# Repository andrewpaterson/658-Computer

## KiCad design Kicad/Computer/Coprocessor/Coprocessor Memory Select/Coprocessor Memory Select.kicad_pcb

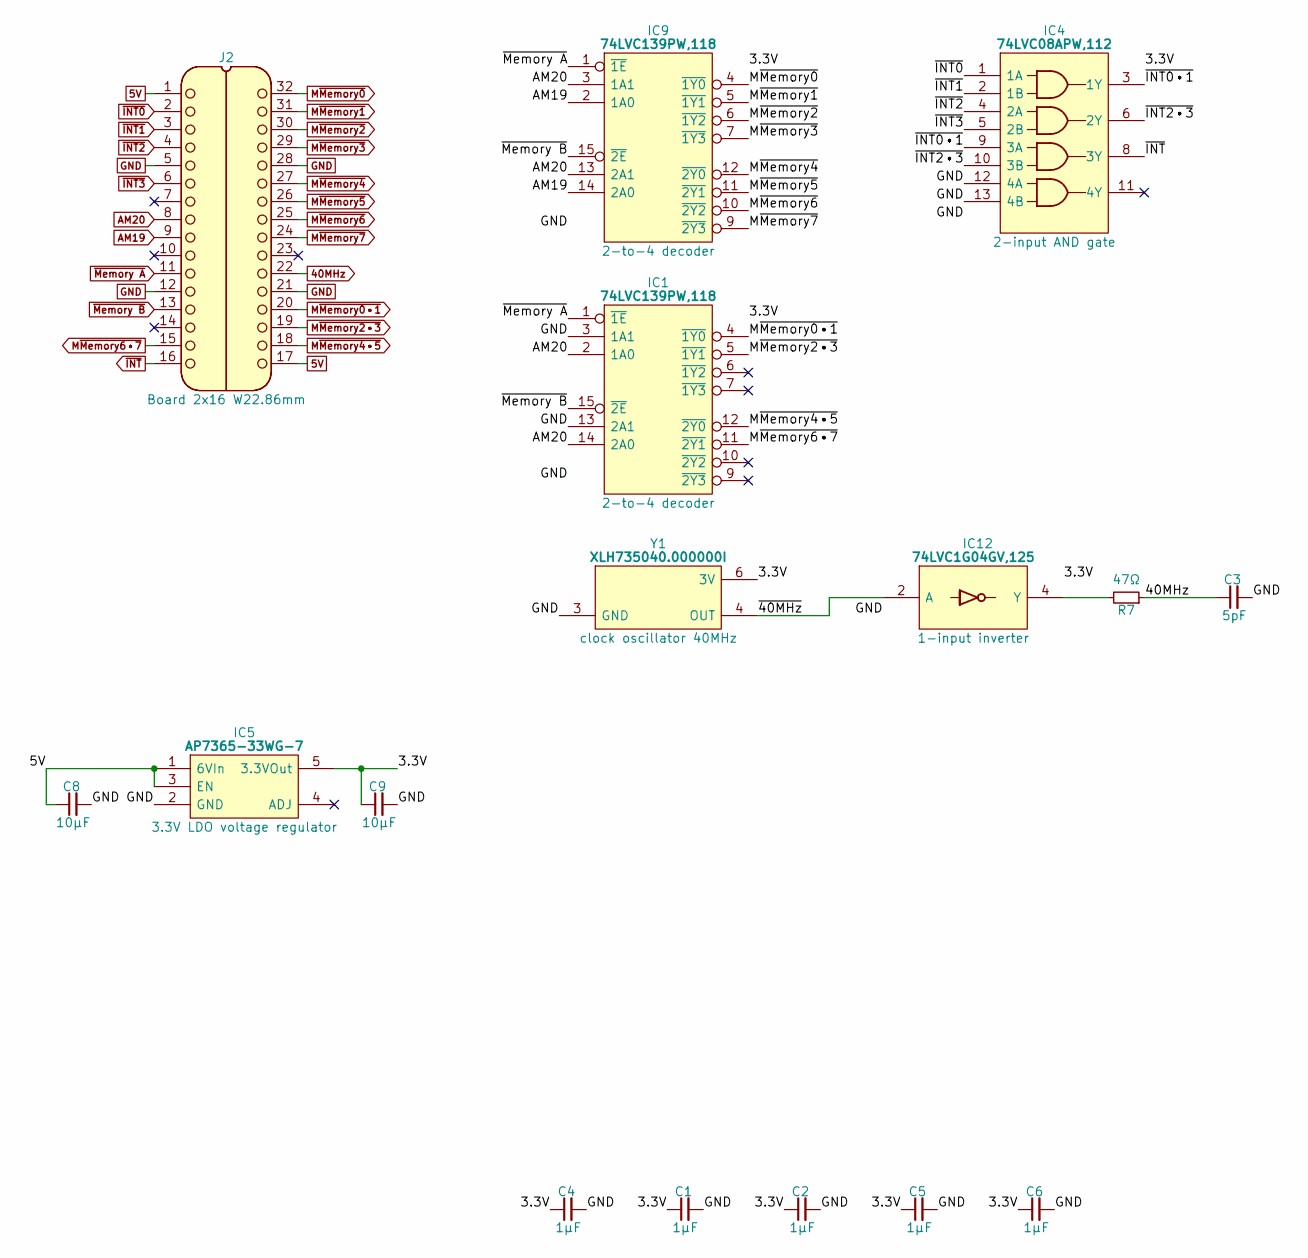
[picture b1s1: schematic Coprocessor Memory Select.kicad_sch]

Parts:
C1, C2, C4, C5, C6: 1μF; C_0805
C3: 5pF; C_0805
C8, C9: 10µF; C_0805
IC1, IC9: 74LVC139PW,118; SOP65P640X110-16N; Mouser Part Number 771-74LVC139PW-T
IC4: 74LVC08APW,112; SOP65P640X110-14N; Manufacturer_Part_Number 74LVC08APW,112; Mouser Part Number 771-74LVC08APW
IC5: AP7365-33WG-7; SOT95P285X130-5N; Manufacturer_Part_Number AP7365-33WG-7; Mouser Part Number 621-AP7365-33WG-7
IC12: 74LVC1G04GV,125; SOT95P275X110-5N; Manufacturer_Part_Number 74LVC1G04GV,125; Mouser Part Number 771-74LVC1G04GV
J2: Board 2x16 W22.86mm; DIP-32_Board_W22.86mm
R7: 47Ω; R_0805
Y1: XLH735040.000000I; XLH736074250000I; Manufacturer_Part_Number XLH735040.000000I; Mouser Part Number 972-LH735040.000000I

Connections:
5V: C8.1, IC5.1 (6VIn), IC5.3 (EN), J2.1, J2.17
40MHz: C3.1, J2.22, R7.1
/3.3V: C1.1, C2.1, C4.1, C5.1, C6.1, C9.1, IC1.16 (3V), IC4.14 (3V), IC5.5 (3.3VOut), IC9.16 (3V), IC12.5 (3V), Y1.6 (3V)
/~40MHz: IC12.2 (A), Y1.4 (OUT)
/~INT0•1: IC4.3 (1Y), IC4.9 (3A)
/~INT2•3: IC4.6 (2Y), IC4.10 (3B)
AM19: IC9.2 (1A0), IC9.14 (2A0), J2.9
AM20: IC1.2 (1A0), IC1.14 (2A0), IC9.3 (1A1), IC9.13 (2A1), J2.8
GND: C1.2, C2.2, C3.2, C4.2, C5.2, C6.2, C8.2, C9.2, IC1.3 (1A1), IC1.8 (GND), IC1.13 (2A1), IC4.7 (GND), IC4.12 (4A), IC4.13 (4B), IC5.2 (GND), IC9.8 (GND), IC12.3 (GND), J2.5, J2.12, J2.21, J2.28, Y1.3 (GND)
M~Memory0: IC9.4 (~1Y0), J2.32
M~Memory0•1: IC1.4 (~1Y0), J2.20
M~Memory1: IC9.5 (~1Y1), J2.31
M~Memory2: IC9.6 (~1Y2), J2.30
M~Memory2•3: IC1.5 (~1Y1), J2.19
M~Memory3: IC9.7 (~1Y3), J2.29
M~Memory4: IC9.12 (~2Y0), J2.27
M~Memory4•5: IC1.12 (~2Y0), J2.18
M~Memory5: IC9.11 (~2Y1), J2.26
M~Memory6: IC9.10 (~2Y2), J2.25
M~Memory6•7: IC1.11 (~2Y1), J2.15
M~Memory7: IC9.9 (~2Y3), J2.24
unnamed: IC12.4 (Y), R7.2
~INT0: IC4.1 (1A), J2.2
~INT1: IC4.2 (1B), J2.3
~INT2: IC4.4 (2A), J2.4
~INT3: IC4.5 (2B), J2.6
~INT: IC4.8 (3Y), J2.16
~Memory A: IC1.1 (~1E), IC9.1 (~1E), J2.11
~Memory B: IC1.15 (~2E), IC9.15 (~2E), J2.13

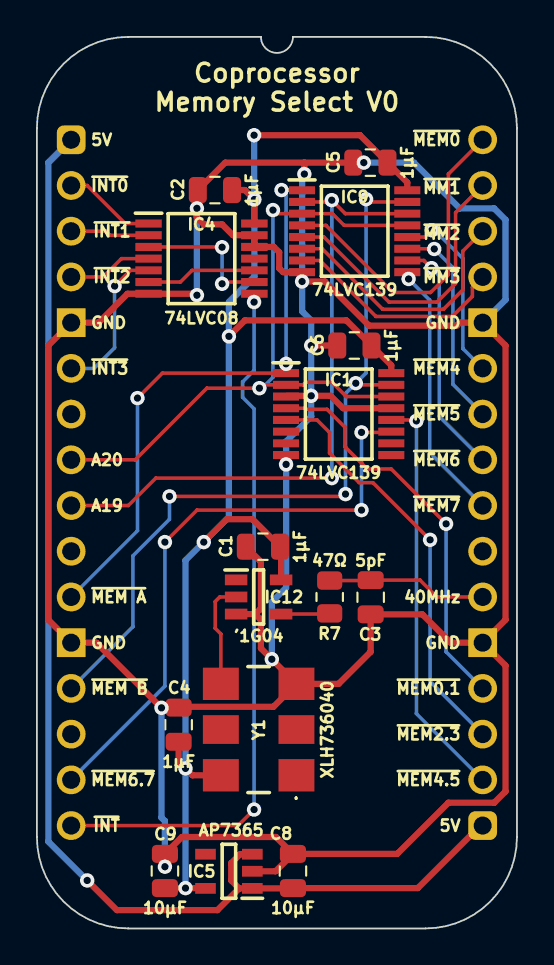
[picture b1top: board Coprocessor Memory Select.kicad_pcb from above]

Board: 2 copper layers, 26.7 x 49.5 mm, 16 parts (0 on the bottom side), 29 nets.

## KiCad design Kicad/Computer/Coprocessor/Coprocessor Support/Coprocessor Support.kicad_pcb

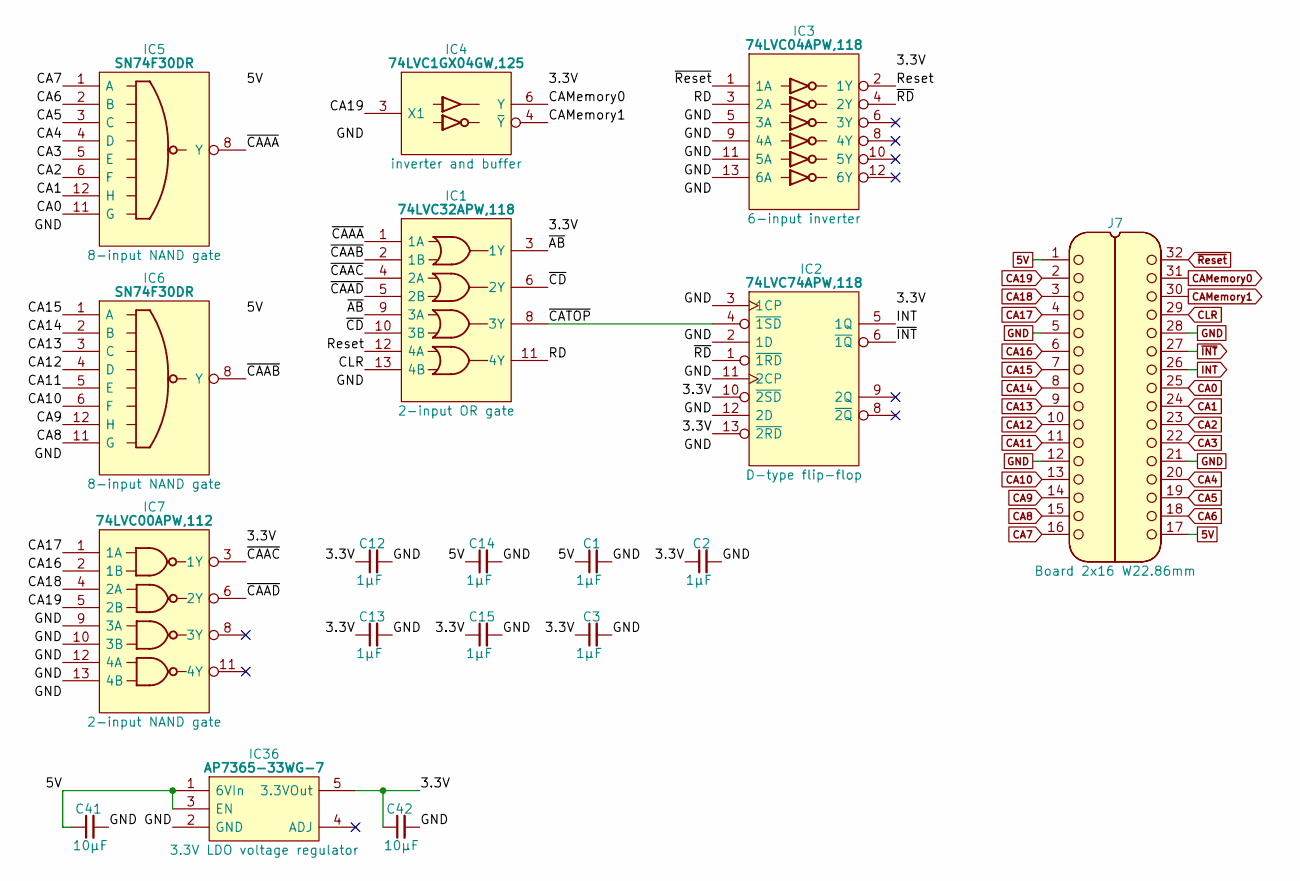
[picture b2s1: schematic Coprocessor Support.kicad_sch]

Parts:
C1, C2, C3, C12, C13, C14, C15: 1µF; C_0805
C41, C42: 10μF; C_0805
IC1: 74LVC32APW,118; SOP65P640X110-14N; Manufacturer_Part_Number 74LVC32APW,118; Mouser Part Number 771-74LVC32APW-T
IC2: 74LVC74APW,118; SOP65P640X110-14N; Mouser Part Number 771-74LVC74APW-T
IC3: 74LVC04APW,118; SOP65P640X110-14N; Manufacturer_Part_Number 74LVC04APW,118; Mouser Part Number 771-74LVC04APW-T
IC4: 74LVC1GX04GW,125; SOP65P210X110-6N; Manufacturer_Part_Number 74LVC1GX04GW,125; Mouser Part Number 771-74LVC1GX04GW-G
IC5, IC6: SN74F30DR; SOIC127P600X175-14N; Manufacturer_Part_Number SN74F30DR; Mouser Part Number 595-SN74F30DR
IC7: 74LVC00APW,112; SOP65P640X110-14N; Mouser Part Number 771-74LVC00APW
IC36: AP7365-33WG-7; SOT95P285X130-5N; Manufacturer_Part_Number AP7365-33WG-7; Mouser Part Number 621-AP7365-33WG-7
J7: Board 2x16 W22.86mm; DIP-32_Board_W22.86mm

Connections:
5V: C1.1, C14.1, C41.1, IC5.14 (5V), IC6.14 (5V), IC36.1 (6VIn), IC36.3 (EN), J7.1, J7.17
/3.3V: C2.1, C3.1, C12.1, C13.1, C15.1, C42.1, IC1.14 (3V), IC2.10 (~2SD), IC2.13 (~2RD), IC2.14 (3V), IC3.14 (3V), IC4.5 (3V), IC7.14 (3V), IC36.5 (3.3VOut)
/RD: IC1.11 (4Y), IC3.3 (2A)
/Reset: IC1.12 (4A), IC3.2 (1Y)
/~AB: IC1.3 (1Y), IC1.9 (3A)
/~CAAA: IC1.1 (1A), IC5.8 (Y)
/~CAAB: IC1.2 (1B), IC6.8 (Y)
/~CAAC: IC1.4 (2A), IC7.3 (1Y)
/~CAAD: IC1.5 (2B), IC7.6 (2Y)
/~CATOP: IC1.8 (3Y), IC2.4 (~1SD)
/~CD: IC1.6 (2Y), IC1.10 (3B)
/~RD: IC2.1 (~1RD), IC3.4 (2Y)
CA0: IC5.11 (G), J7.25
CA1: IC5.12 (H), J7.24
CA2: IC5.6 (F), J7.23
CA3: IC5.5 (E), J7.22
CA4: IC5.4 (D), J7.20
CA5: IC5.3 (C), J7.19
CA6: IC5.2 (B), J7.18
CA7: IC5.1 (A), J7.16
CA8: IC6.11 (G), J7.15
CA9: IC6.12 (H), J7.14
CA10: IC6.6 (F), J7.13
CA11: IC6.5 (E), J7.11
CA12: IC6.4 (D), J7.10
CA13: IC6.3 (C), J7.9
CA14: IC6.2 (B), J7.8
CA15: IC6.1 (A), J7.7
CA16: IC7.2 (1B), J7.6
CA17: IC7.1 (1A), J7.4
CA18: IC7.4 (2A), J7.3
CA19: IC4.3 (X1), IC7.5 (2B), J7.2
CAMemory0: IC4.6 (Y), J7.31
CAMemory1: IC4.4 (~Y), J7.30
CLR: IC1.13 (4B), J7.29
GND: C1.2, C2.2, C3.2, C12.2, C13.2, C14.2, C15.2, C41.2, C42.2, IC1.7 (GND), IC2.2 (1D), IC2.3 (1CP), IC2.7 (GND), IC2.11 (2CP), IC2.12 (2D), IC3.5 (3A), IC3.7 (GND), IC3.9 (4A), IC3.11 (5A), IC3.13 (6A), IC4.2 (GND), IC5.7 (GND), IC6.7 (GND), IC7.7 (GND), IC7.9 (3A), IC7.10 (3B), IC7.12 (4A), IC7.13 (4B), IC36.2 (GND), J7.5, J7.12, J7.21, J7.28
INT: IC2.5 (1Q), J7.26
~INT: IC2.6 (~1Q), J7.27
~Reset: IC3.1 (1A), J7.32

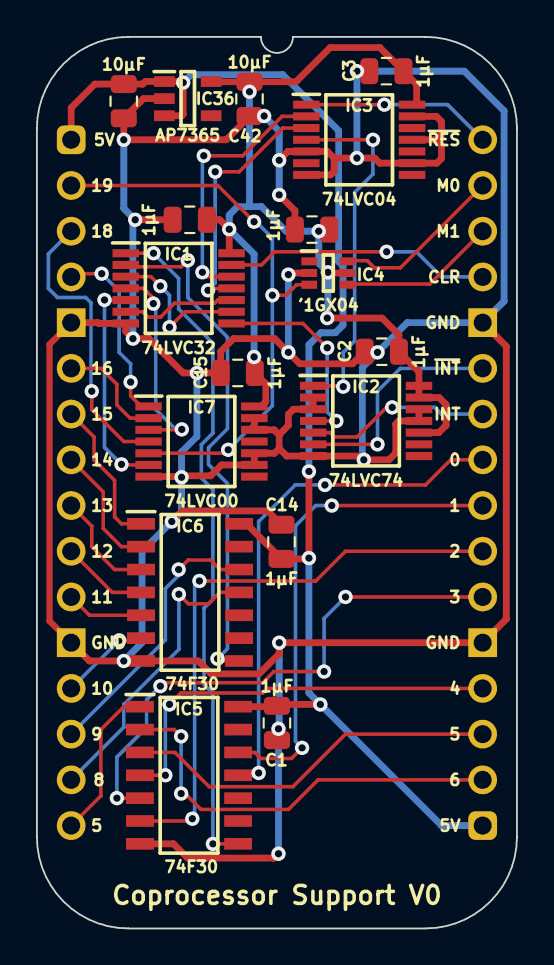
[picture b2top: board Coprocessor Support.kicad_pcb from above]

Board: 2 copper layers, 26.7 x 49.5 mm, 18 parts (0 on the bottom side), 39 nets.

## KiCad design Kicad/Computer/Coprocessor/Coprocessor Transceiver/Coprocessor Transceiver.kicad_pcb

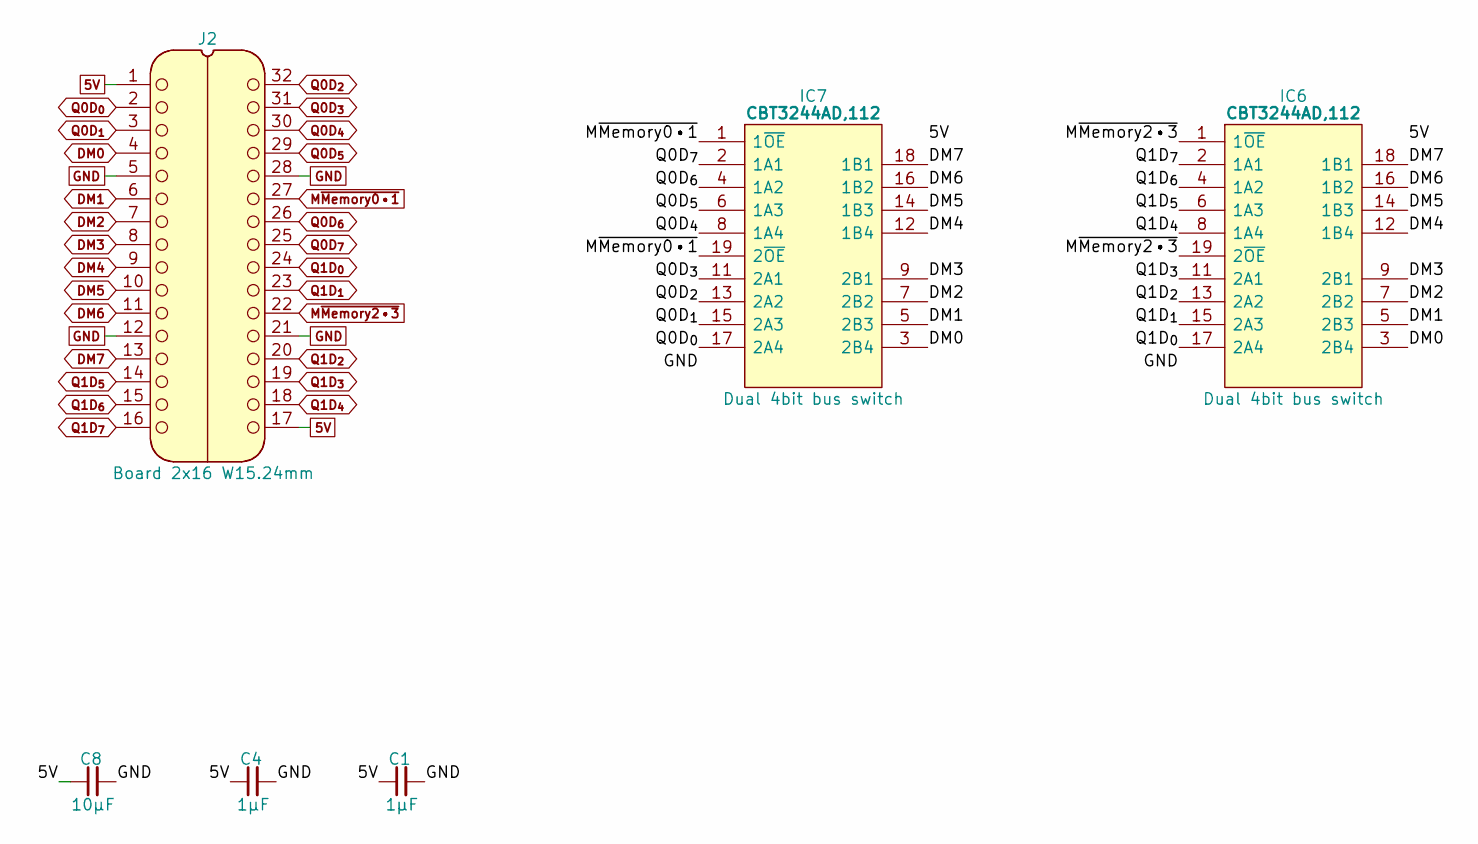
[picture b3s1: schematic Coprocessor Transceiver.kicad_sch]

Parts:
C1, C4: 1μF; C_0805
C8: 10µF; C_0805
IC6, IC7: CBT3244AD,112; SOIC127P1032X265-20N; Manufacturer_Part_Number CBT3244AD,112; Mouser Part Number 771-CBT3244AD
J2: Board 2x16 W15.24mm; DIP-32_Board_W15.24mm

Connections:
5V: C1.1, C4.1, C8.1, IC6.20 (5V), IC7.20 (5V), J2.1, J2.17
DM0: IC6.3 (2B4), IC7.3 (2B4), J2.4
DM1: IC6.5 (2B3), IC7.5 (2B3), J2.6
DM2: IC6.7 (2B2), IC7.7 (2B2), J2.7
DM3: IC6.9 (2B1), IC7.9 (2B1), J2.8
DM4: IC6.12 (1B4), IC7.12 (1B4), J2.9
DM5: IC6.14 (1B3), IC7.14 (1B3), J2.10
DM6: IC6.16 (1B2), IC7.16 (1B2), J2.11
DM7: IC6.18 (1B1), IC7.18 (1B1), J2.13
GND: C1.2, C4.2, C8.2, IC6.10 (GND), IC7.10 (GND), J2.5, J2.12, J2.21, J2.28
M~Memory0•1: IC7.1 (1~OE), IC7.19 (2~OE), J2.27
M~Memory2•3: IC6.1 (1~OE), IC6.19 (2~OE), J2.22
Q0D_{0}: IC7.17 (2A4), J2.2
Q0D_{1}: IC7.15 (2A3), J2.3
Q0D_{2}: IC7.13 (2A2), J2.32
Q0D_{3}: IC7.11 (2A1), J2.31
Q0D_{4}: IC7.8 (1A4), J2.30
Q0D_{5}: IC7.6 (1A3), J2.29
Q0D_{6}: IC7.4 (1A2), J2.26
Q0D_{7}: IC7.2 (1A1), J2.25
Q1D_{0}: IC6.17 (2A4), J2.24
Q1D_{1}: IC6.15 (2A3), J2.23
Q1D_{2}: IC6.13 (2A2), J2.20
Q1D_{3}: IC6.11 (2A1), J2.19
Q1D_{4}: IC6.8 (1A4), J2.18
Q1D_{5}: IC6.6 (1A3), J2.14
Q1D_{6}: IC6.4 (1A2), J2.15
Q1D_{7}: IC6.2 (1A1), J2.16

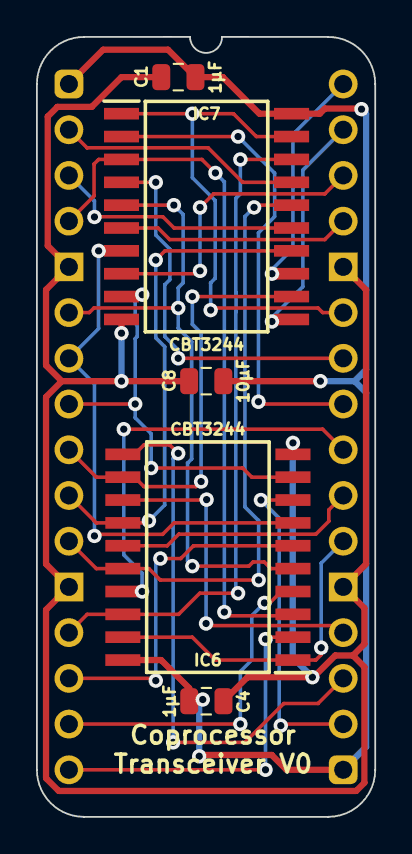
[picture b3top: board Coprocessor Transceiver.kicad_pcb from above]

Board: 2 copper layers, 18.8 x 43.3 mm, 6 parts (0 on the bottom side), 28 nets.

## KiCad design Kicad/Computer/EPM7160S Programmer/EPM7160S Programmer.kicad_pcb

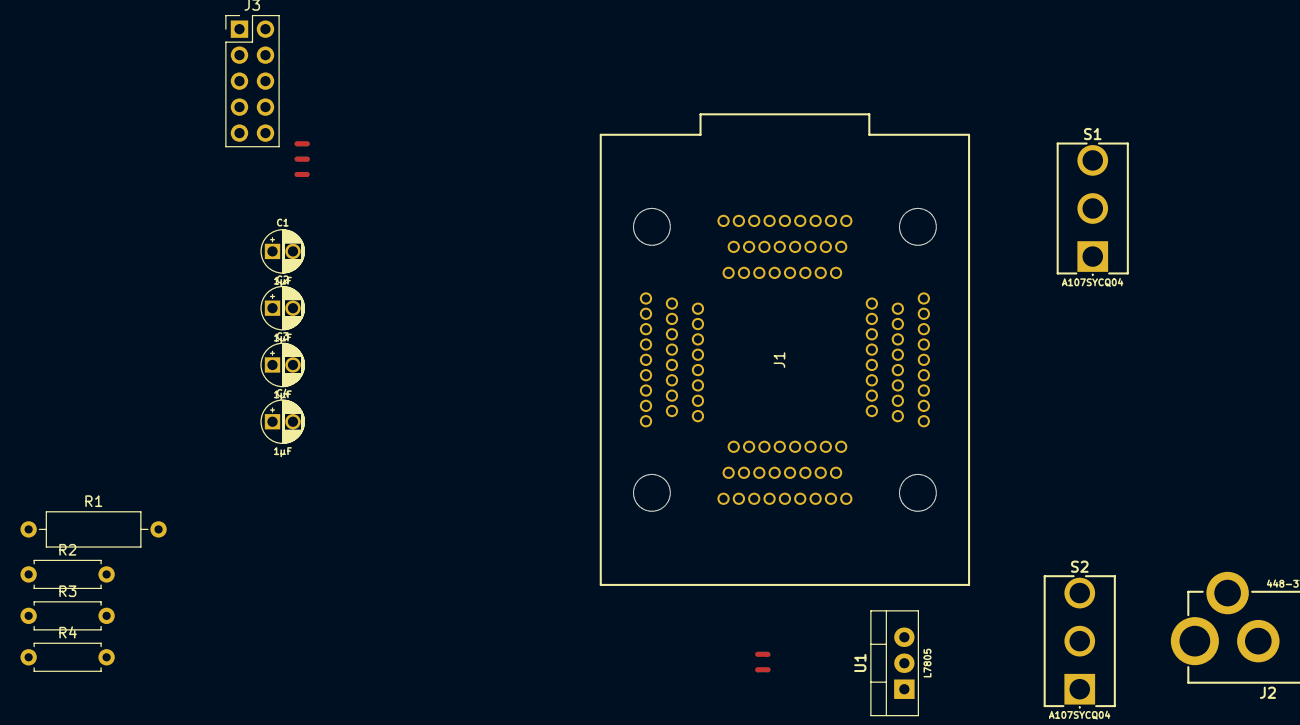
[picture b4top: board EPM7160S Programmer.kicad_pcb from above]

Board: 2 copper layers, 19 parts (0 on the bottom side), 16 nets, no tracks yet.

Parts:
C1, C2, C3, C4: 1μF; CP_Radial_D4.0mm_P2.00mm
J1: AllSocket-QFP-100-14X14-0.5-Clamshell
J2: 448-376; 448376
J3: Conn_02x05_Counter_Clockwise; PinHeader_2x05_P2.54mm_Vertical
NT1, NT2, NT3, NT4, NT5: NetTie_2; NetTie-2_SMD_Pad0.5mm
R1: 100; R_Axial_DIN0309_L9.0mm_D3.2mm_P12.70mm_Horizontal
R2, R3: 6.8K; R_Axial_DIN0207_L6.3mm_D2.5mm_P7.62mm_Horizontal
R4: 2.2K; R_Axial_DIN0207_L6.3mm_D2.5mm_P7.62mm_Horizontal
S1, S2: A107SYCQ04
U1: L7805; TO-220-3_Vertical

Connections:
/5V: NT4.1, NT5.1, R1.2, R3.1, U1.3 (OUT)
/12V: S1.2 (CM), S2.1, U1.1 (IN)
/12V Socket: J2.A1 (VCC), S2.2 (CM)
/GND: C1.2, C2.2, C3.2, C4.2, J1.11, J1.26, J1.38, J1.43, J1.59, J1.74, J1.86, J1.95, J2.B1 (GND), J2.C1 (GND), J3.6, J3.10, R2.1, U1.2 (GND)
/INPUT/GCLK1: J1.87, NT3.2
/INPUT/GCLRn: J1.89, NT2.2
/INPUT/OE1: J1.88, R4.2
/INPUT/OE2/GCLK2: J1.90, NT1.2
/TCK: J1.62, J3.1, R2.2
/TDI: J1.4, J3.5
/TDO: J1.73, J3.2
/TMS: J1.15, J3.3, R3.2
/VCCINT: C1.1, C2.1, J1.39, J1.91, NT4.2
/VCCIO: C3.1, C4.1, J1.3, J1.18, J1.34, J1.51, J1.66, J1.82, NT5.2
unnamed: J3.9, R1.1
unnamed: R4.1, S1.1

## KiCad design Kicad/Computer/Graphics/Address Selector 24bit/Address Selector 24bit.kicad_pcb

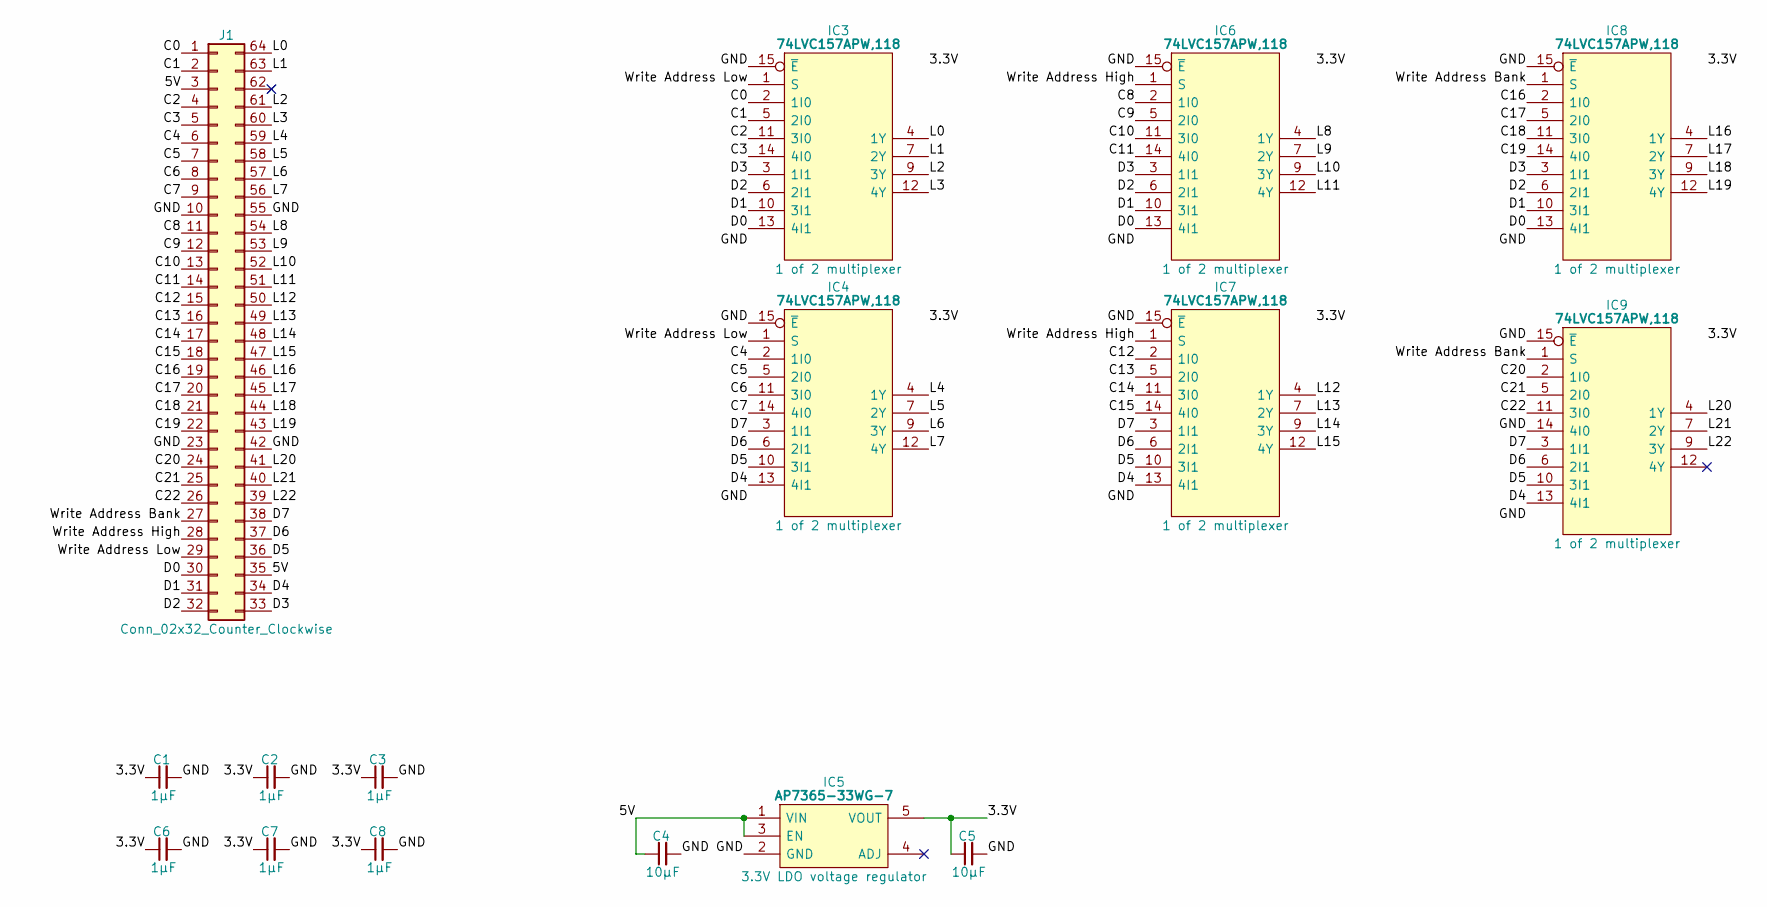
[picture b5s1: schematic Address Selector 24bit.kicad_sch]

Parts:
C1, C2, C3, C6, C7, C8: 1μF; C_0805
C4, C5: 10µF; C_0805
IC3, IC4, IC6, IC7, IC8, IC9: 74LVC157APW,118; SOP65P640X110-16N; Mouser Part Number 771-74LVC157APW-T
IC5: AP7365-33WG-7; SOT95P285X130-5N; Manufacturer_Part_Number AP7365-33WG-7; Mouser Part Number 621-AP7365-33WG-7
J1: Conn_02x32_Counter_Clockwise; DIP-64_Board_W15.24mm

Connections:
/3.3V: C1.1, C2.1, C3.1, C5.1, C6.1, C7.1, C8.1, IC3.16 (3V), IC4.16 (3V), IC5.5 (VOUT), IC6.16 (3V), IC7.16 (3V), IC8.16 (3V), IC9.16 (3V)
/5V: C4.1, IC5.1 (VIN), IC5.3 (EN), J1.3, J1.35
/C0: IC3.2 (1I0), J1.1
/C1: IC3.5 (2I0), J1.2
/C2: IC3.11 (3I0), J1.4
/C3: IC3.14 (4I0), J1.5
/C4: IC4.2 (1I0), J1.6
/C5: IC4.5 (2I0), J1.7
/C6: IC4.11 (3I0), J1.8
/C7: IC4.14 (4I0), J1.9
/C8: IC6.2 (1I0), J1.11
/C9: IC6.5 (2I0), J1.12
/C10: IC6.11 (3I0), J1.13
/C11: IC6.14 (4I0), J1.14
/C12: IC7.2 (1I0), J1.15
/C13: IC7.5 (2I0), J1.16
/C14: IC7.11 (3I0), J1.17
/C15: IC7.14 (4I0), J1.18
/C16: IC8.2 (1I0), J1.19
/C17: IC8.5 (2I0), J1.20
/C18: IC8.11 (3I0), J1.21
/C19: IC8.14 (4I0), J1.22
/C20: IC9.2 (1I0), J1.24
/C21: IC9.5 (2I0), J1.25
/C22: IC9.11 (3I0), J1.26
/D0: IC3.13 (4I1), IC6.13 (4I1), IC8.13 (4I1), J1.30
/D1: IC3.10 (3I1), IC6.10 (3I1), IC8.10 (3I1), J1.31
/D2: IC3.6 (2I1), IC6.6 (2I1), IC8.6 (2I1), J1.32
/D3: IC3.3 (1I1), IC6.3 (1I1), IC8.3 (1I1), J1.33
/D4: IC4.13 (4I1), IC7.13 (4I1), IC9.13 (4I1), J1.34
/D5: IC4.10 (3I1), IC7.10 (3I1), IC9.10 (3I1), J1.36
/D6: IC4.6 (2I1), IC7.6 (2I1), IC9.6 (2I1), J1.37
/D7: IC4.3 (1I1), IC7.3 (1I1), IC9.3 (1I1), J1.38
/GND: C1.2, C2.2, C3.2, C4.2, C5.2, C6.2, C7.2, C8.2, IC3.8 (GND), IC3.15 (~E), IC4.8 (GND), IC4.15 (~E), IC5.2 (GND), IC6.8 (GND), IC6.15 (~E), IC7.8 (GND), IC7.15 (~E), IC8.8 (GND), IC8.15 (~E), IC9.8 (GND), IC9.14 (4I0), IC9.15 (~E), J1.10, J1.23, J1.42, J1.55
/L0: IC3.4 (1Y), J1.64
/L1: IC3.7 (2Y), J1.63
/L2: IC3.9 (3Y), J1.61
/L3: IC3.12 (4Y), J1.60
/L4: IC4.4 (1Y), J1.59
/L5: IC4.7 (2Y), J1.58
/L6: IC4.9 (3Y), J1.57
/L7: IC4.12 (4Y), J1.56
/L8: IC6.4 (1Y), J1.54
/L9: IC6.7 (2Y), J1.53
/L10: IC6.9 (3Y), J1.52
/L11: IC6.12 (4Y), J1.51
/L12: IC7.4 (1Y), J1.50
/L13: IC7.7 (2Y), J1.49
/L14: IC7.9 (3Y), J1.48
/L15: IC7.12 (4Y), J1.47
/L16: IC8.4 (1Y), J1.46
/L17: IC8.7 (2Y), J1.45
/L18: IC8.9 (3Y), J1.44
/L19: IC8.12 (4Y), J1.43
/L20: IC9.4 (1Y), J1.41
/L21: IC9.7 (2Y), J1.40
/L22: IC9.9 (3Y), J1.39
/Write Address Bank: IC8.1 (S), IC9.1 (S), J1.27
/Write Address High: IC6.1 (S), IC7.1 (S), J1.28
/Write Address Low: IC3.1 (S), IC4.1 (S), J1.29

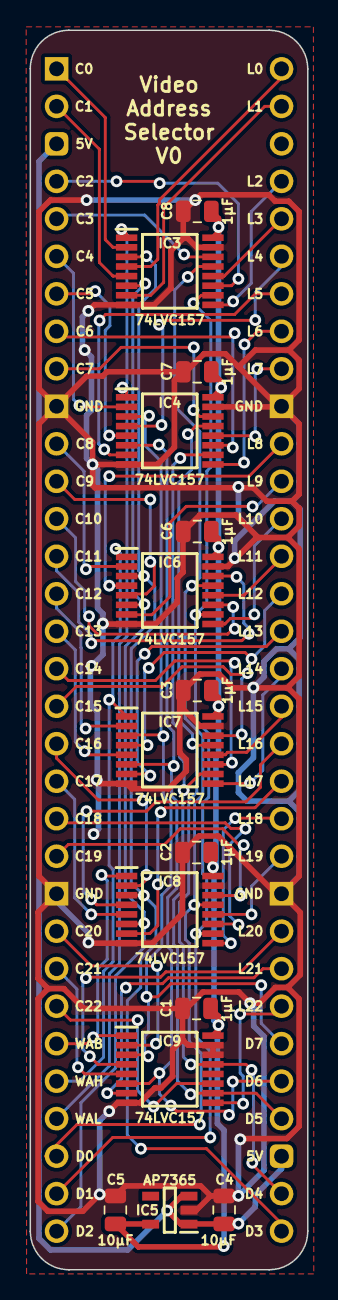
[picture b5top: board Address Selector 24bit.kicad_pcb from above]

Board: 2 copper layers, 18.8 x 84.0 mm, 16 parts (0 on the bottom side), 60 nets.

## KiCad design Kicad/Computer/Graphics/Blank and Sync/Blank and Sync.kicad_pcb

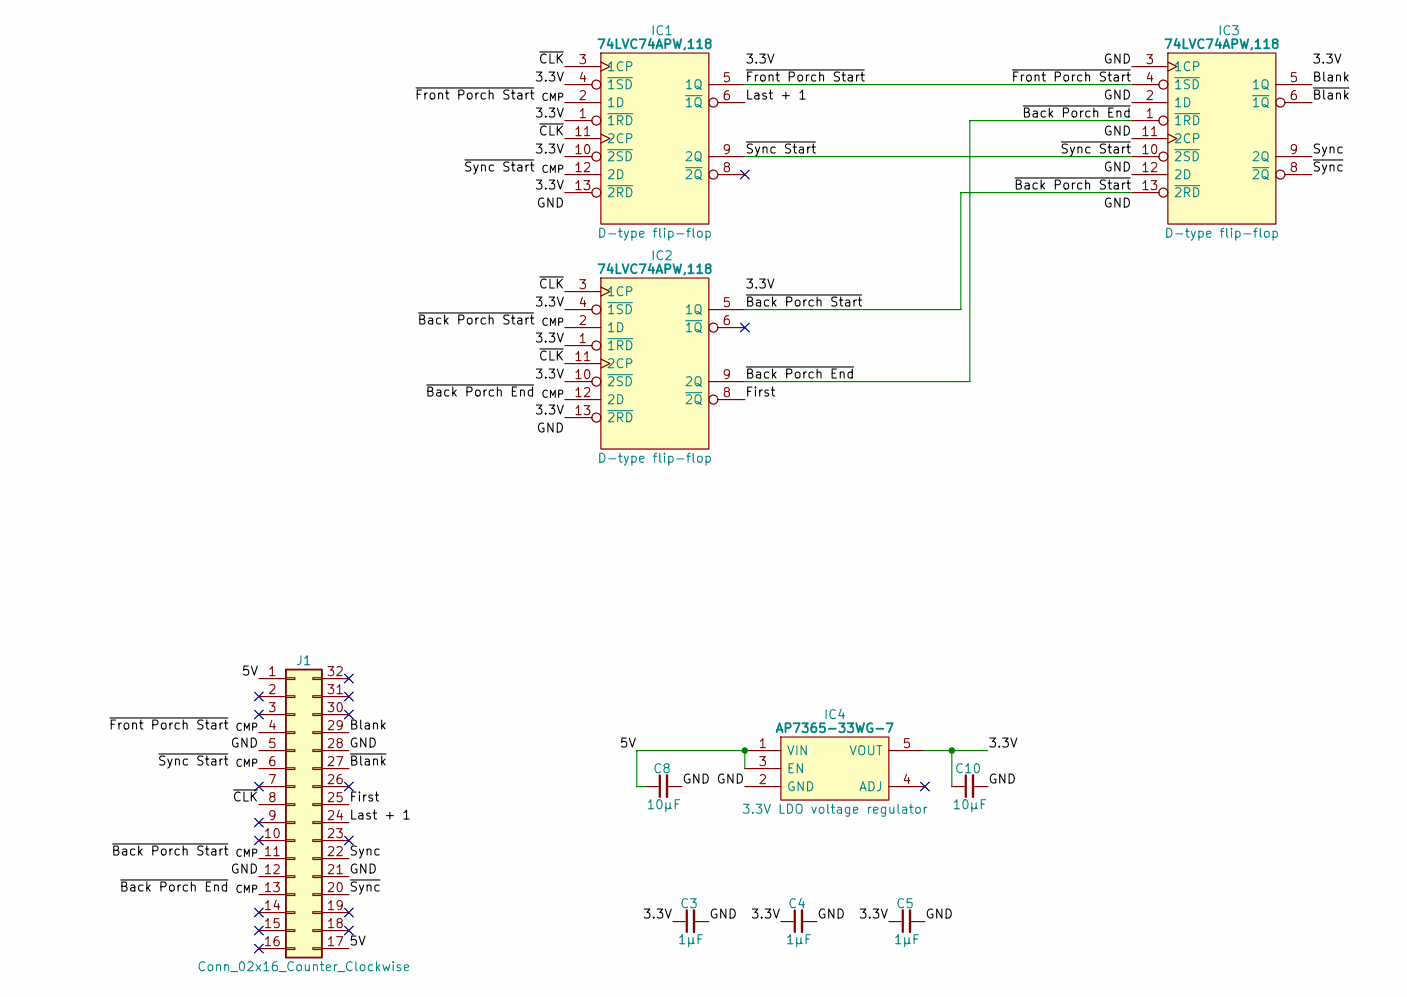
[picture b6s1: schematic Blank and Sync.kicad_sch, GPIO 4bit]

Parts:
C3, C4, C5: 1μF; C_0805
C8, C10: 10µF; C_0805
IC1, IC2, IC3: 74LVC74APW,118; SOP65P640X110-14N; Mouser Part Number 771-74LVC74APW-T
IC4: AP7365-33WG-7; SOT95P285X130-5N; Manufacturer_Part_Number AP7365-33WG-7; Mouser Part Number 621-AP7365-33WG-7
J1: Conn_02x16_Counter_Clockwise; DIP-32_Board_W15.24mm

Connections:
/3.3V: C3.1, C4.1, C5.1, C10.1, IC1.1 (~1RD), IC1.4 (~1SD), IC1.10 (~2SD), IC1.13 (~2RD), IC1.14 (3V), IC2.1 (~1RD), IC2.4 (~1SD), IC2.10 (~2SD), IC2.13 (~2RD), IC2.14 (3V), IC3.14 (3V), IC4.5 (VOUT)
/5V: C8.1, IC4.1 (VIN), IC4.3 (EN), J1.1, J1.17
/Blank: IC3.5 (1Q), J1.29
/First: IC2.8 (~2Q), J1.25
/GND: C3.2, C4.2, C5.2, C8.2, C10.2, IC1.7 (GND), IC2.7 (GND), IC3.2 (1D), IC3.3 (1CP), IC3.7 (GND), IC3.11 (2CP), IC3.12 (2D), IC4.2 (GND), J1.5, J1.12, J1.21, J1.28
/Last + 1: IC1.6 (~1Q), J1.24
/Sync: IC3.9 (2Q), J1.22
/~Back Porch End: IC2.9 (2Q), IC3.1 (~1RD)
/~Back Porch End _{CMP}: IC2.12 (2D), J1.13
/~Back Porch Start: IC2.5 (1Q), IC3.13 (~2RD)
/~Back Porch Start _{CMP}: IC2.2 (1D), J1.11
/~Blank: IC3.6 (~1Q), J1.27
/~CLK: IC1.3 (1CP), IC1.11 (2CP), IC2.3 (1CP), IC2.11 (2CP), J1.8
/~Front Porch Start: IC1.5 (1Q), IC3.4 (~1SD)
/~Front Porch Start _{CMP}: IC1.2 (1D), J1.4
/~Sync Start: IC1.9 (2Q), IC3.10 (~2SD)
/~Sync Start _{CMP}: IC1.12 (2D), J1.6
/~Sync: IC3.8 (~2Q), J1.20

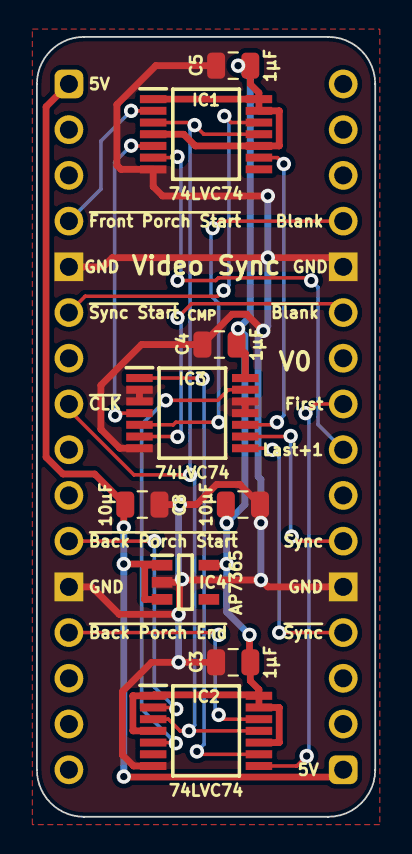
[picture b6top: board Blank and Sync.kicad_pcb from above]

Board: 2 copper layers, 18.8 x 43.3 mm, 10 parts (0 on the bottom side), 18 nets.
